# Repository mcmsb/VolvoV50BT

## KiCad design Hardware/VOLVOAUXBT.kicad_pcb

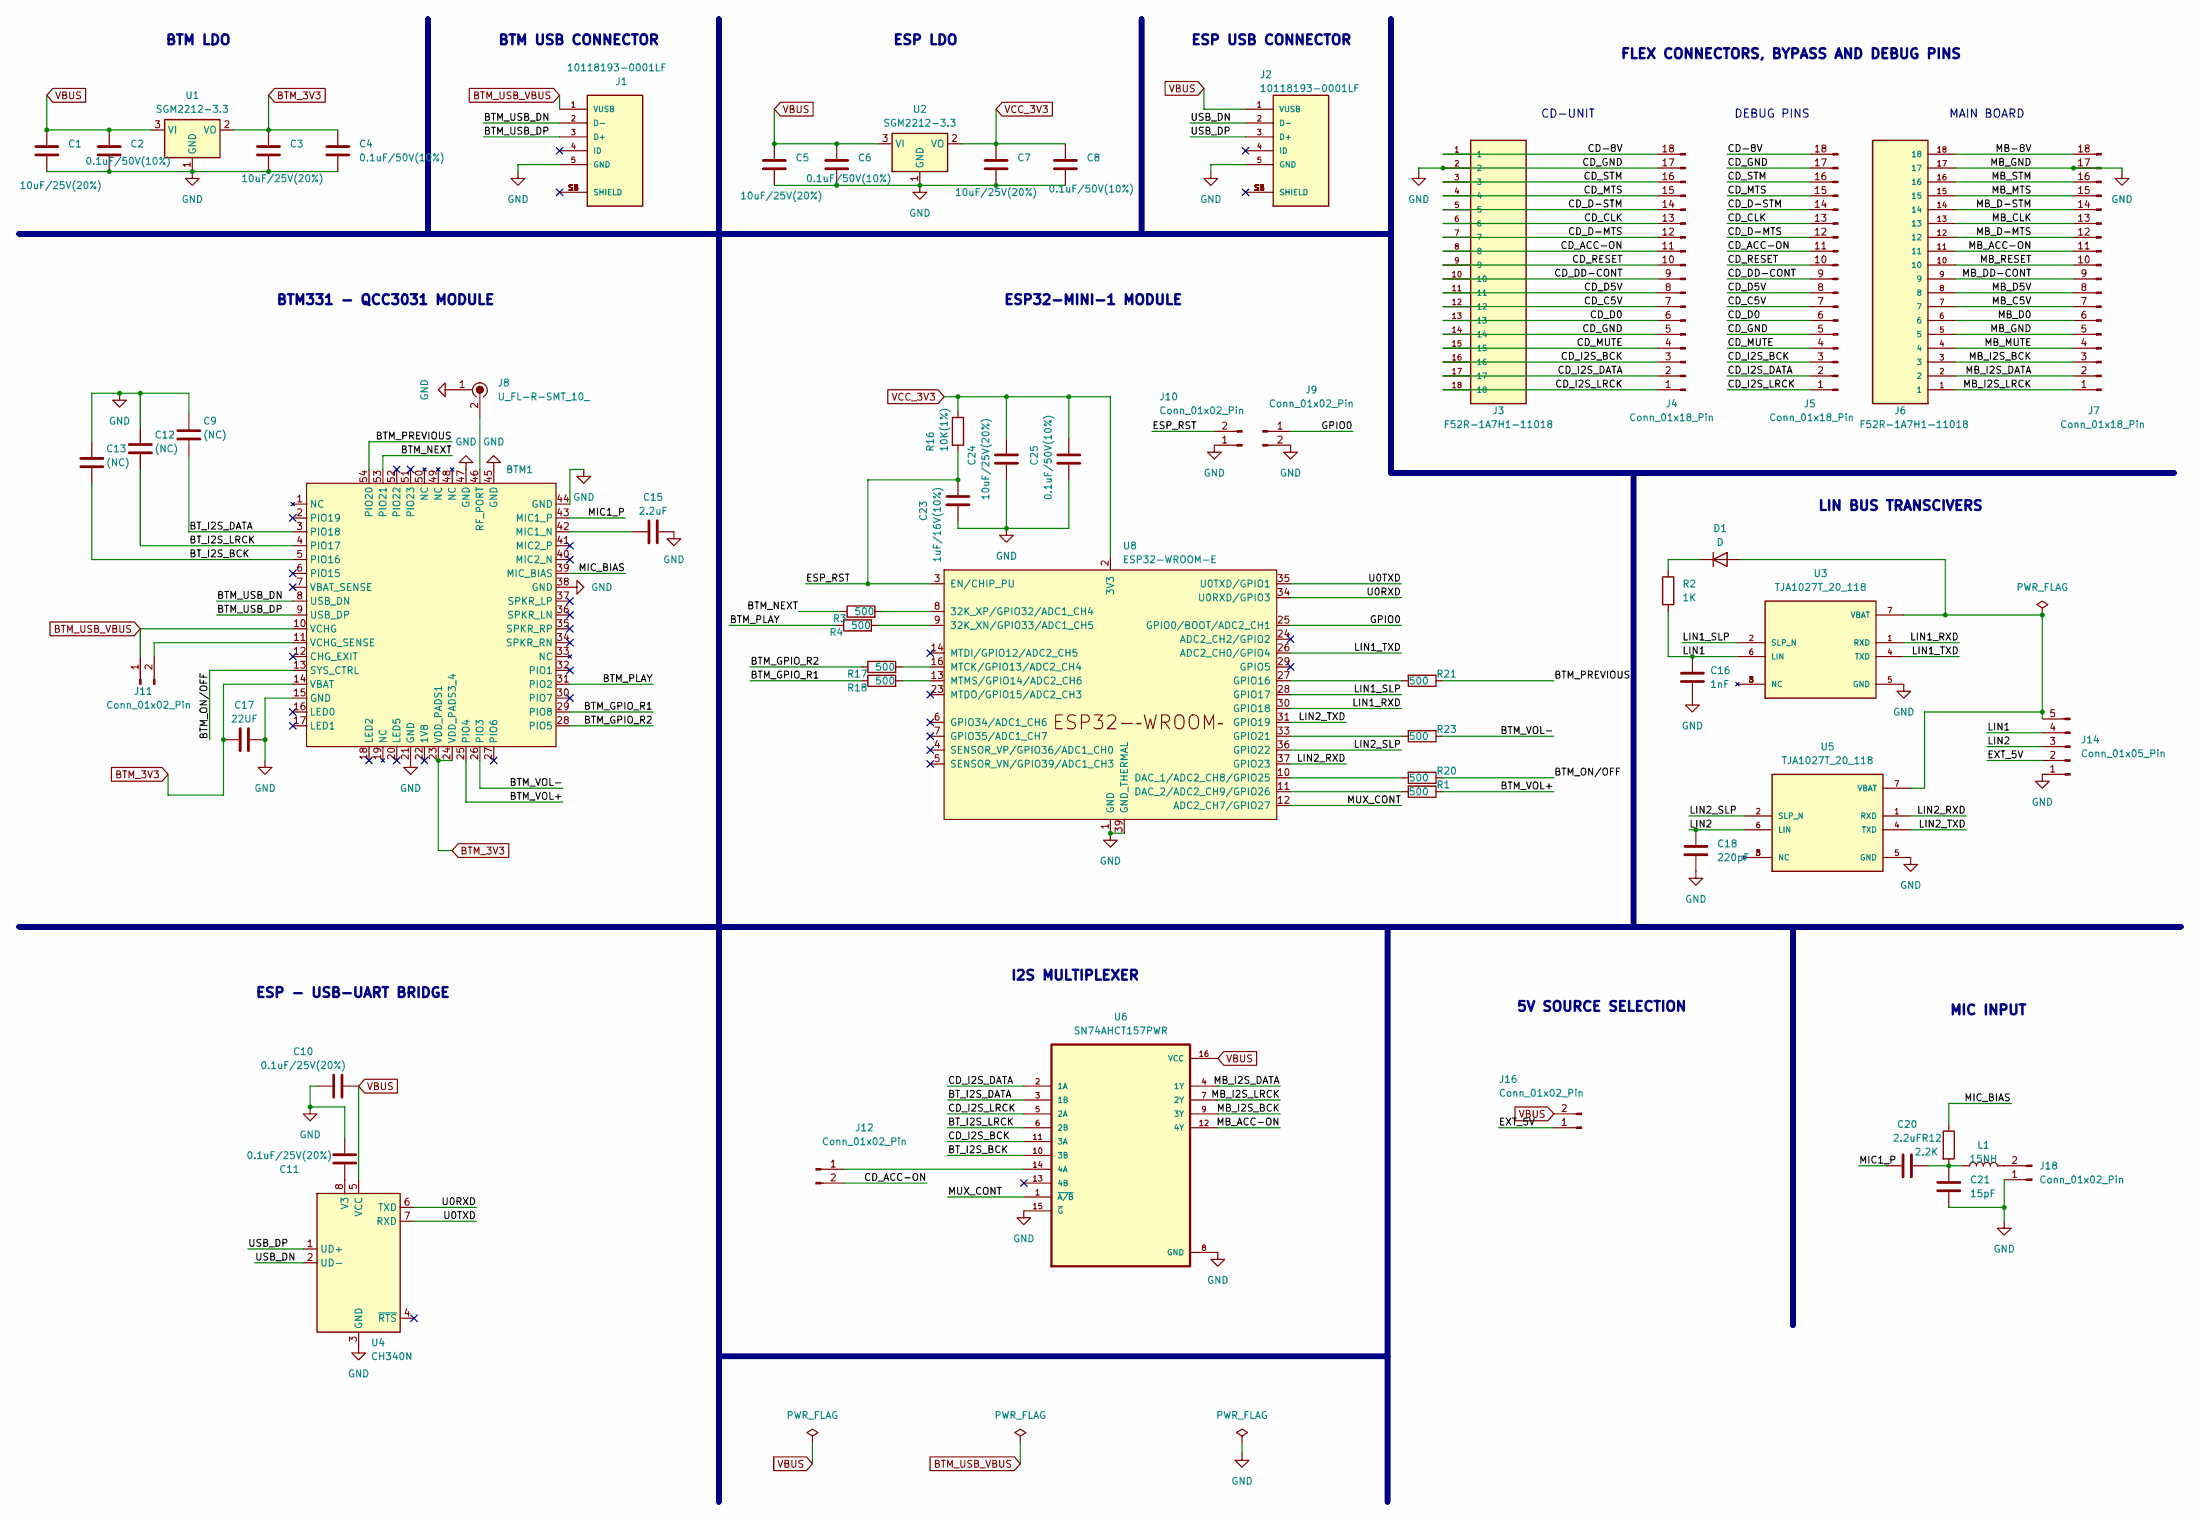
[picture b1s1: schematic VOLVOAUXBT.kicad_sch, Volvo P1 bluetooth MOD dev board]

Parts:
BTM1: BTM331
C1, C3, C5, C7, C24: 10uF/25V(20%); C_1206_3216Metric
C2, C4, C6, C8, C25: 0.1uF/50V(10%); C_1206_3216Metric
C9, C12, C13: (NC); C_1206_3216Metric_Pad1.33x1.80mm_HandSolder
C10, C11: 0.1uF/25V(20%); C_1206_3216Metric
C15, C20: 2.2uF; C_0805_2012Metric
C16: 1nF; C_1206_3216Metric_Pad1.33x1.80mm_HandSolder
C17: 22UF; C_1206_3216Metric
C18: 220pF; C_1206_3216Metric_Pad1.33x1.80mm_HandSolder
C21: 15pF; C_0603_1608Metric
C23: 1uF/16V(10%); C_1206_3216Metric
D1: D; D_1206_3216Metric
J1, J2: 10118193-0001LF; AMPHENOL_10118193-0001LF; PARTREV E
J3, J6: F52R-1A7H1-11018; AMPHENOL_F52R-1A7H1-11018; PARTREV B
J4, J5, J7: Conn_01x18_Pin; PinHeader_1x18_P2.54mm_Vertical
J8: U_FL-R-SMT_10_; U.FL_Hirose_U.FL-R-SMT-1_Vertical; MPN U.FL-R-SMT(10); Digi-Key_PN H9161CT-ND
J9, J10, J11, J12, J16, J18: Conn_01x02_Pin; PinHeader_1x02_P2.54mm_Vertical
J14: Conn_01x05_Pin; JST_XH_B5B-XH-AM_1x05_P2.50mm_Vertical
L1: 15NH; L_1206_3216Metric_Pad1.22x1.90mm_HandSolder
R1, R3, R4, R17, R18, R20, R21, R23: 500; R_0603_1608Metric
R2: 1K; R_0603_1608Metric
R12: 2.2K; R_0603_1608Metric
R16: 10K(1%); R_0603_1608Metric
U1, U2: SGM2212-3.3; SOT-223-3_TabPin2
U3, U5: TJA1027T_20_118; SOIC127P600X175-8N
U4: CH340N; SOP-8_3.9x4.9mm_P1.27mm
U6: SN74AHCT157PWR; SOP65P640X120-16N
U8: ESP32-WROOM-E; ESP32-WROOM-32E

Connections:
/BTM_GPIO_R1: BTM1.29 (PIO8), R18.1
/BTM_GPIO_R2: BTM1.28 (PIO5), R17.1
/BTM_NEXT: BTM1.53 (PIO21), R3.1
/BTM_ON/OFF: BTM1.13 (SYS_CTRL), R20.1
/BTM_PLAY: BTM1.31 (PIO2), R4.1
/BTM_PREVIOUS: BTM1.54 (PIO20), R21.1
/BTM_USB_DN: BTM1.8 (USB_DN), J1.2 (D-)
/BTM_USB_DP: BTM1.9 (USB_DP), J1.3 (D+)
/BTM_VOL+: BTM1.25 (PIO4), R1.1
/BTM_VOL-: BTM1.26 (PIO3), R23.1
/BT_I2S_BCK: BTM1.5 (PIO16), C13.2, U6.10 (3B)
/BT_I2S_DATA: BTM1.3 (PIO18), C9.2, U6.3 (1B)
/BT_I2S_LRCK: BTM1.4 (PIO17), C12.2, U6.6 (2B)
/CD-8V: J3.1, J4.18, J5.18
/CD_ACC-ON: J3.8, J4.11, J5.11, J12.2
/CD_C5V: J3.12, J4.7, J5.7
/CD_CLK: J3.6, J4.13, J5.13
/CD_D0: J3.13, J4.6, J5.6
/CD_D5V: J3.11, J4.8, J5.8
/CD_D-MTS: J3.7, J4.12, J5.12
/CD_D-STM: J3.5, J4.14, J5.14
/CD_DD-CONT: J3.10, J4.9, J5.9
/CD_I2S_BCK: J3.16, J4.3, J5.3, U6.11 (3A)
/CD_I2S_DATA: J3.17, J4.2, J5.2, U6.2 (1A)
/CD_I2S_LRCK: J3.18, J4.1, J5.1, U6.5 (2A)
/CD_MTS: J3.4, J4.15, J5.15
/CD_MUTE: J3.15, J4.4, J5.4
/CD_RESET: J3.9, J4.10, J5.10
/CD_STM: J3.3, J4.16, J5.16
/ESP_RST: C23.1, J10.2, R16.2, U8.3 (EN/CHIP_PU)
/EXT_5V: J14.2, J16.1
/GPIO0: J9.1, U8.25 (GPIO0/BOOT/ADC2_CH1)
/LIN1: C16.1, J14.4, R2.2, U3.6 (LIN)
/LIN1_RXD: U3.1 (RXD), U8.30 (GPIO18)
/LIN1_SLP: U3.2 (SLP_N), U8.28 (GPIO17)
/LIN1_TXD: U3.4 (TXD), U8.26 (ADC2_CH0/GPIO4)
/LIN2: C18.1, J14.3, U5.6 (LIN)
/LIN2_RXD: U5.1 (RXD), U8.37 (GPIO23)
/LIN2_SLP: U5.2 (SLP_N), U8.36 (GPIO22)
/LIN2_TXD: U5.4 (TXD), U8.31 (GPIO19)
/MB-8V: J6.18, J7.18
/MB_ACC-ON: J6.11, J7.11, U6.12 (4Y)
/MB_C5V: J6.7, J7.7
/MB_CLK: J6.13, J7.13
/MB_D0: J6.6, J7.6
/MB_D5V: J6.8, J7.8
/MB_D-MTS: J6.12, J7.12
/MB_D-STM: J6.14, J7.14
/MB_DD-CONT: J6.9, J7.9
/MB_I2S_BCK: J6.3, J7.3, U6.9 (3Y)
/MB_I2S_DATA: J6.2, J7.2, U6.4 (1Y)
/MB_I2S_LRCK: J6.1, J7.1, U6.7 (2Y)
/MB_MTS: J6.15, J7.15
/MB_MUTE: J6.4, J7.4
/MB_RESET: J6.10, J7.10
/MB_STM: J6.16, J7.16
/MIC1_P: BTM1.43 (MIC1_P), C20.1
/MIC_BIAS: BTM1.39 (MIC_BIAS), R12.1
/MUX_CONT: U6.1 (~A/B), U8.12 (ADC2_CH7/GPIO27)
/U0RXD: U4.6 (TXD), U8.34 (U0RXD/GPIO3)
/U0TXD: U4.7 (RXD), U8.35 (U0TXD/GPIO1)
/USB_DN: J2.2 (D-), U4.2 (UD-)
/USB_DP: J2.3 (D+), U4.1 (UD+)
BTM_3V3: BTM1.14 (VBAT), BTM1.23 (VDD_PADS1), BTM1.24 (VDD_PADS3_4), C3.1, C4.1, C17.1, U1.2 (VO)
BTM_USB_VBUS: BTM1.10 (VCHG), J1.1 (VUSB), J11.1
GND: BTM1.15 (GND), BTM1.21 (GND), BTM1.38 (GND), BTM1.44 (GND), BTM1.45 (GND), BTM1.47 (GND), C1.2, C2.2, C3.2, C4.2, C5.2, C6.2, C7.2, C8.2, C9.1, C10.1, C11.2, C12.1, C13.1, C15.2, C16.2, C17.2, C18.2, C21.2, C23.2, C24.2, C25.2, J1.5 (GND), J2.5 (GND), J3.2, J3.14, J4.5, J4.17, J5.5, J5.17, J6.5, J6.17, J7.5, J7.17, J8.1, J9.2, J10.1, J14.1, J18.1, U1.1 (GND), U2.1 (GND), U3.5 (GND), U4.3 (GND), U5.5 (GND), U6.8 (GND), U6.15 (~G), U8.1 (GND), U8.15 (GND), U8.38 (GND), U8.39 (GND_THERMAL)
unnamed: BTM1.42 (MIC1_N), C15.1
unnamed: BTM1.46 (RF_PORT), J8.2
unnamed: BTM1.11 (VCHG_SENSE), J11.2
unnamed: C20.2, C21.1, L1.1, R12.2
unnamed: D1.2 (A), J14.5, U3.7 (VBAT), U5.7 (VBAT)
unnamed: D1.1 (K), R2.1
unnamed: J12.1, U6.14 (4A)
unnamed: J18.2, L1.2
unnamed: C11.1, U4.8 (V3)
unnamed: R4.2, U8.9 (32K_XN/GPIO33/ADC1_CH5)
unnamed: R3.2, U8.8 (32K_XP/GPIO32/ADC1_CH4)
unnamed: R20.2, U8.10 (DAC_1/ADC2_CH8/GPIO25)
unnamed: R1.2, U8.11 (DAC_2/ADC2_CH9/GPIO26)
unnamed: R21.2, U8.27 (GPIO16)
unnamed: R23.2, U8.33 (GPIO21)
unnamed: R17.2, U8.16 (MTCK/GPIO13/ADC2_CH4)
unnamed: R18.2, U8.13 (MTMS/GPIO14/ADC2_CH6)
VBUS: C1.1, C2.1, C5.1, C6.1, C10.2, J2.1 (VUSB), J16.2, U1.3 (VI), U2.3 (VI), U4.5 (VCC), U6.16 (VCC)
VCC_3V3: C7.1, C8.1, C24.1, C25.1, R16.1, U2.2 (VO), U8.2 (3V3)

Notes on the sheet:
I2S MULTIPLEXER
BTM USB CONNECTOR
BTM LDO
5V SOURCE SELECTION
MIC INPUT
MAIN BOARD
ESP32-MINI-1 MODULE
ESP USB CONNECTOR
BTM331 - QCC3031 MODULE
CD-UNIT
ESP - USB-UART BRIDGE
LIN BUS TRANSCIVERS
DEBUG PINS
ESP LDO
FLEX CONNECTORS, BYPASS AND DEBUG PINS

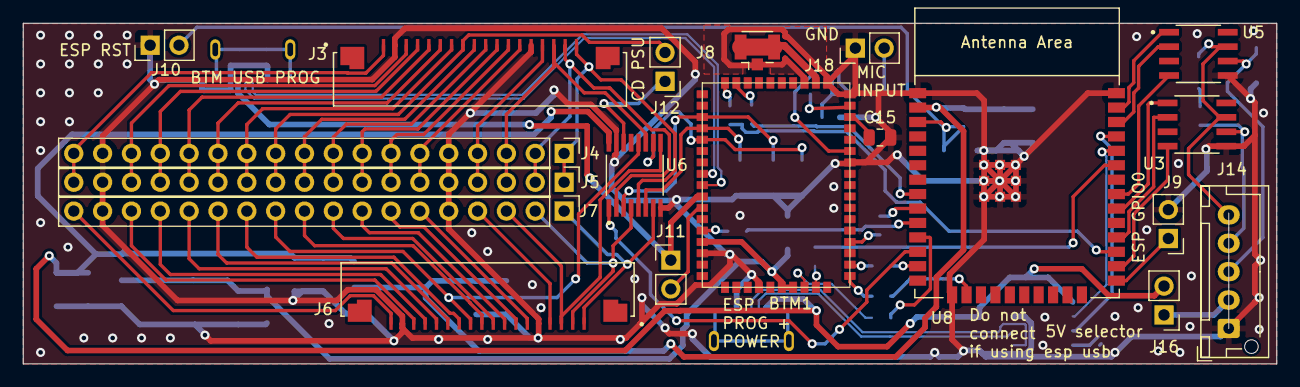
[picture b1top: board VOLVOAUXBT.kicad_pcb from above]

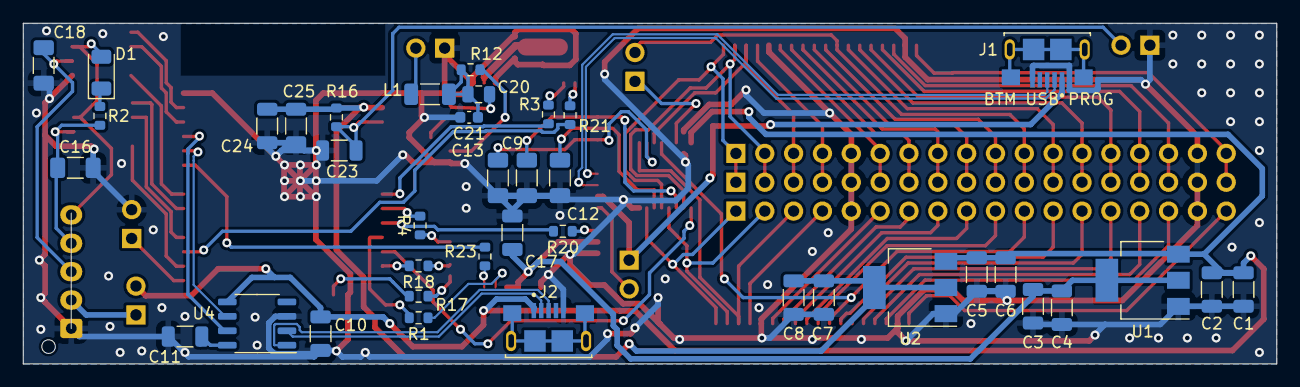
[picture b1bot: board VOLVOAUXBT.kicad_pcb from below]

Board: 2 copper layers, 110.4 x 30.0 mm, 58 parts (39 on the bottom side), 85 nets.

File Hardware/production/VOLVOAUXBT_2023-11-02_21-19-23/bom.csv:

Designator,Footprint,Quantity,Value,LCSC Part #
BTM1,BTM331,1,~,
"C1, C24, C3, C5, C7",1206,5,10uF/25V(20%),
"C10, C11",1206,2,0.1uF/25V(20%),
"C12, C13, C9",1206,3,(NC),
"C15, C20",0805,2,2.2uF,
"C16, C18",1206,2,C,
C17,1206,1,22UF,
"C2, C25, C4, C6, C8",1206,5,0.1uF/50V(10%),
C21,0603,1,15pF,
C23,1206,1,1uF/16V(10%),
D1,1206,1,D,
"J1, J2",AMPHENOL_10118193-0001LF,2,10118193-0001LF,
"J10, J11, J12, J16, J18, J9",PinHeader_1x02_P2.54mm_Vertical,6,Conn_01x02_Pin,
J14,JST_XH_B5B-XH-AM_1x05_P2.50mm_Vertical,1,Conn_01x05_Pin,
"J3, J6",AMPHENOL_F52R-1A7H1-11018,2,F52R-1A7H1-11018,
"J4, J5, J7",PinHeader_1x18_P2.54mm_Vertical,3,Conn_01x18_Pin,
J8,U.FL_Hirose_U.FL-R-SMT-1_Vertical,1,U_FL-R-SMT_10_,U.FL-R-SMT(10)
L1,1206,1,15NH,
"R1, R17, R18, R20, R21, R23, R3, R4",0603,8,500,
R12,0603,1,2.2K,
R16,0603,1,10K(1%),
R2,0603,1,1K,
"U1, U2",SOT-223-3_TabPin2,2,SGM2212-3.3,
"U3, U5",SOIC127P600X175-8N,2,TJA1027T_20_118,
U4,SOP-8_3.9x4.9mm_P1.27mm,1,CH340N,
U6,SOP65P640X120-16N,1,SN74AHCT157PWR,
U8,ESP32-WROOM-32E,1,ESP32-WROOM-E,

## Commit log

2023-10-01 Schematic V0.1 - No pcb
2023-10-01 Readme
2023-10-02 PCB layout wihtout traces
2023-10-21 Before swap to wroom
2023-10-21 Swap to ESP32-wroom-32e. Updated PCB too
2023-10-21 First iteration of PCB routing
2023-10-22 Crappy routing, too cramped
2023-10-23 Routing with low side clearence. Pending accurate measurments for produciton
2023-11-03 XST set to 2.5mm. Swapping for 2.54mm
